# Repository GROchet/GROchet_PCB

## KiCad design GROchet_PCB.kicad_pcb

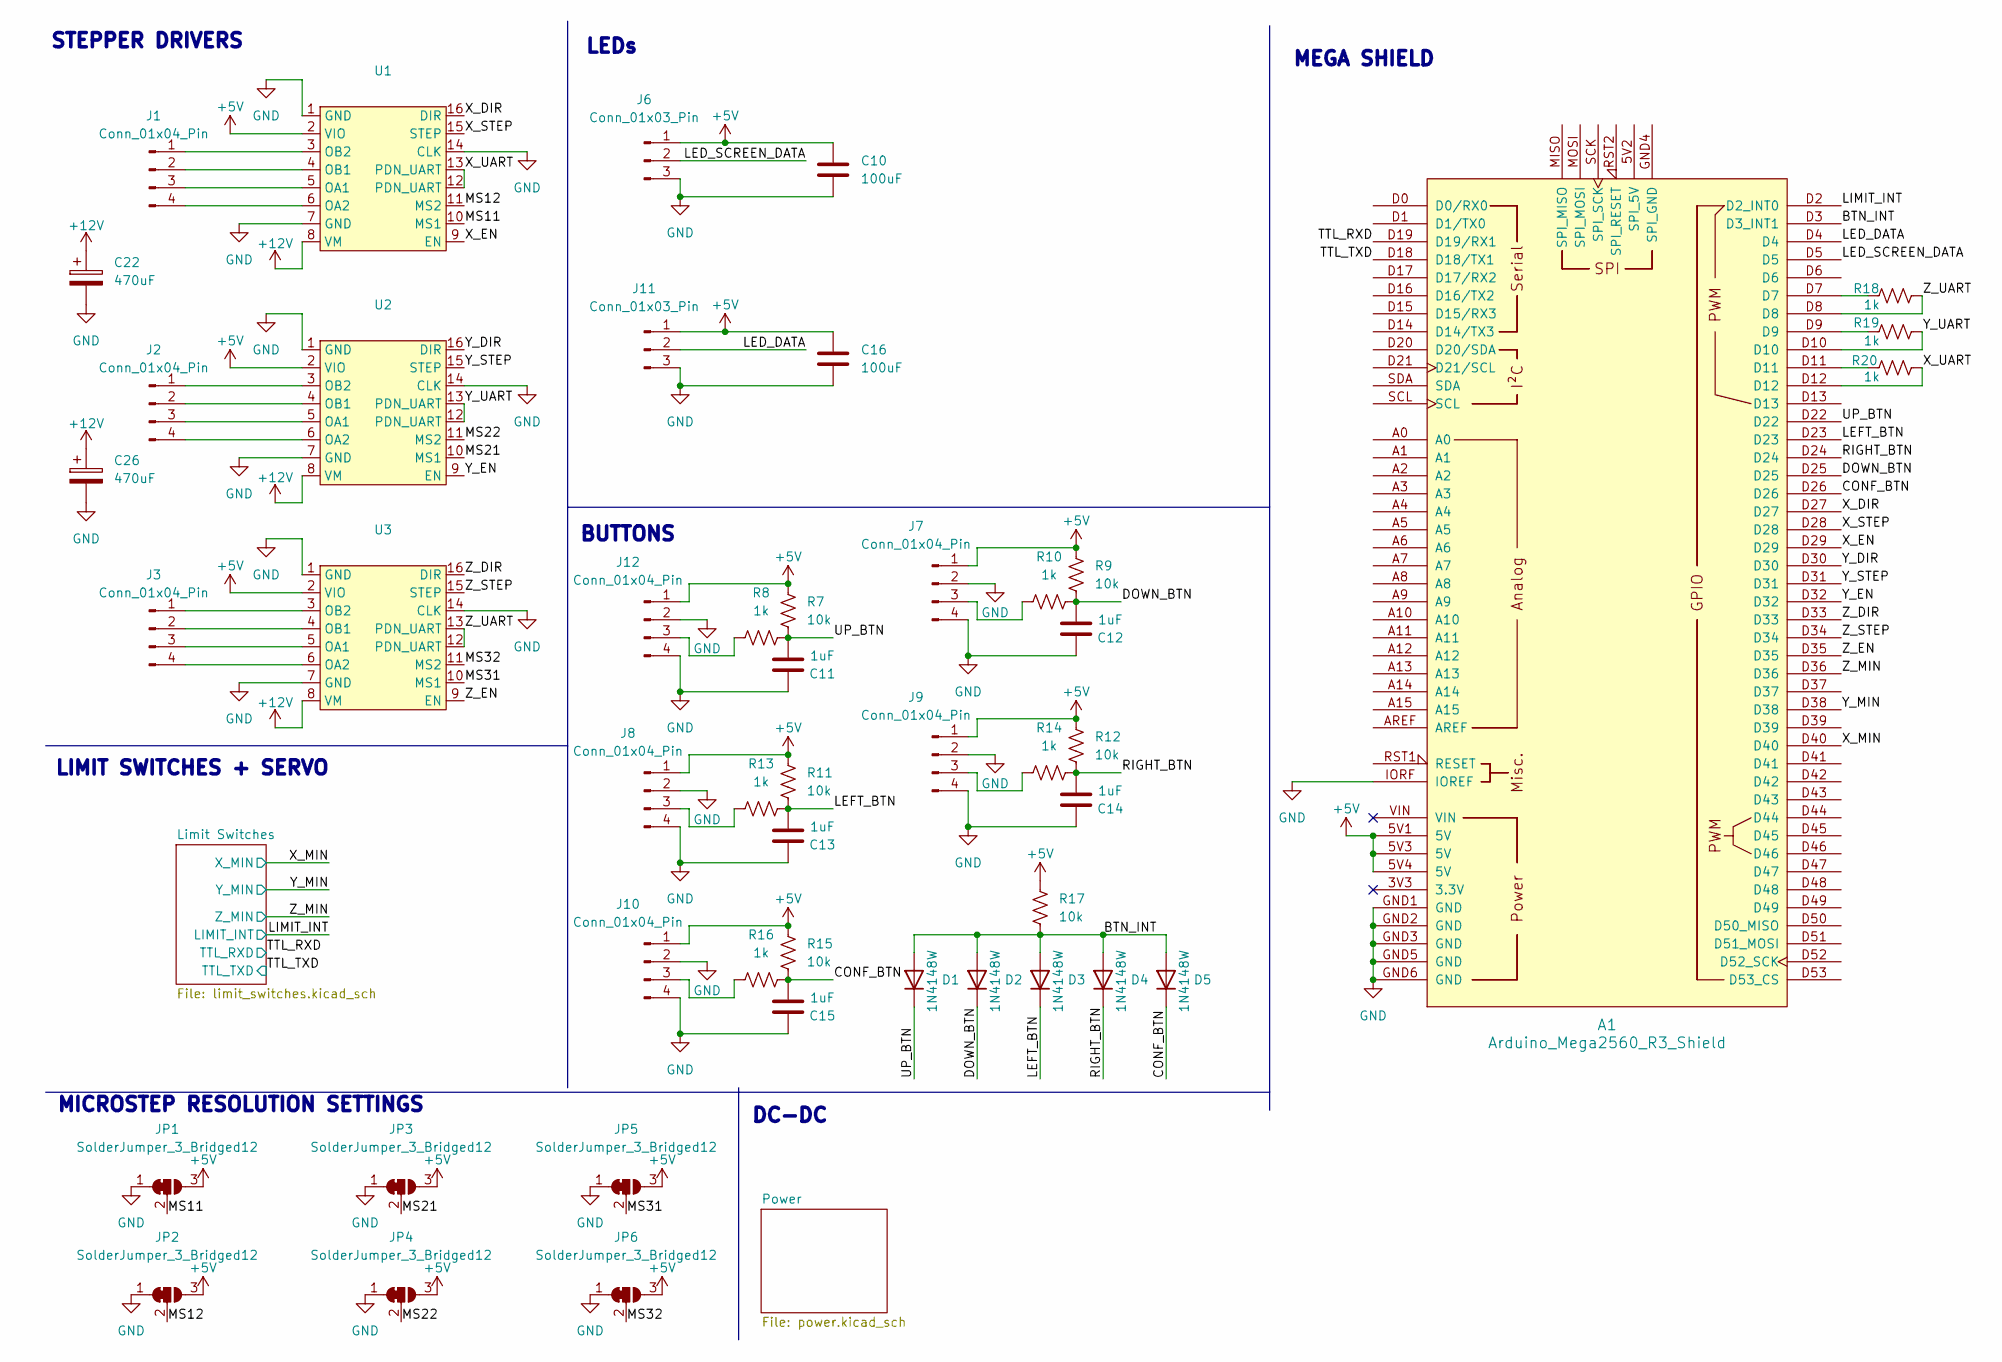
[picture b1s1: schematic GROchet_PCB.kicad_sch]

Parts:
A1: Arduino_Mega2560_R3_Shield
C10, C16: 100uF; C_1206_3216Metric; LCSC C7432784
C11, C12, C13, C14, C15: 1uF; C_0603_1608Metric_Pad1.08x0.95mm_HandSolder
C22, C26: 470uF; CP_Radial_D8.0mm_P3.50mm; LCSC C2873977
D1, D2, D3, D4, D5: 1N4148W; D_SOD-123; LCSC C83528
J1, J2, J3, J7, J8, J9, J10, J12: Conn_01x04_Pin; JST_EH_B4B-EH-A_1x04_P2.50mm_Vertical; LCSC C160258
J6, J11: Conn_01x03_Pin; JST_EH_B3B-EH-A_1x03_P2.50mm_Vertical; LCSC C144394
JP1, JP2, JP3, JP4, JP5, JP6: SolderJumper_3_Bridged12; SolderJumper-3_P1.3mm_Bridged12_RoundedPad1.0x1.5mm
R7, R9, R11, R12, R15, R17: 10k; R_0603_1608Metric_Pad0.98x0.95mm_HandSolder; LCSC C98220
R8, R10, R13, R14, R16, R18, R19, R20: 1k; R_0603_1608Metric_Pad0.98x0.95mm_HandSolder; LCSC C2907113
U1, U2, U3: TMC2208

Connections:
+5V: A1.5V1 (5V), A1.5V3 (5V), A1.5V4 (5V), C10.1, C16.1, J6.1, J7.1, J8.1, J9.1, J10.1, J11.1, J12.1, JP1.3 (B), JP2.3 (B), JP3.3 (B), JP4.3 (B), JP5.3 (B), JP6.3 (B), R7.1, R9.1, R11.1, R12.1, R15.1, R17.1, U1.2 (VIO), U2.2 (VIO), U3.2 (VIO); also elsewhere on the board
+12V: C22.1, C26.1, U1.8 (VM), U2.8 (VM), U3.8 (VM); also elsewhere on the board
/BTN_INT: A1.D3 (D3_INT1), D1.2 (A), D2.2 (A), D3.2 (A), D4.2 (A), D5.2 (A), R17.2
/CONF_BTN: A1.D26, C15.2, D5.1 (K), R15.2, R16.2
/DOWN_BTN: A1.D25, C12.2, D2.1 (K), R9.2, R10.2
/LED_DATA: A1.D4, J11.2
/LED_SCREEN_DATA: A1.D5, J6.2
/LEFT_BTN: A1.D23, C13.2, D3.1 (K), R11.2, R13.2
/LIMIT_INT: A1.D2 (D2_INT0); also elsewhere on the board
/MS11: JP1.2 (C), U1.10 (MS1)
/MS12: JP2.2 (C), U1.11 (MS2)
/MS21: JP3.2 (C), U2.10 (MS1)
/MS22: JP4.2 (C), U2.11 (MS2)
/MS31: JP5.2 (C), U3.10 (MS1)
/MS32: JP6.2 (C), U3.11 (MS2)
/RIGHT_BTN: A1.D24, C14.2, D4.1 (K), R12.2, R14.2
/TTL_RXD: A1.D19 (D19/RX1); also elsewhere on the board
/TTL_TXD: A1.D18 (D18/TX1); also elsewhere on the board
/UP_BTN: A1.D22, C11.2, D1.1 (K), R7.2, R8.2
/X_DIR: A1.D27, U1.16 (DIR)
/X_EN: A1.D29, U1.9 (EN)
/X_MIN: A1.D40; also elsewhere on the board
/X_STEP: A1.D28, U1.15 (STEP)
/X_UART: A1.D12, R20.2, U1.12 (PDN_UART), U1.13 (PDN_UART)
/Y_DIR: A1.D30, U2.16 (DIR)
/Y_EN: A1.D32, U2.9 (EN)
/Y_MIN: A1.D38; also elsewhere on the board
/Y_STEP: A1.D31, U2.15 (STEP)
/Y_UART: A1.D10, R19.2, U2.12 (PDN_UART), U2.13 (PDN_UART)
/Z_DIR: A1.D33, U3.16 (DIR)
/Z_EN: A1.D35, U3.9 (EN)
/Z_MIN: A1.D36; also elsewhere on the board
/Z_STEP: A1.D34, U3.15 (STEP)
/Z_UART: A1.D8, R18.2, U3.12 (PDN_UART), U3.13 (PDN_UART)
GND: A1.GND1 (GND), A1.GND2 (GND), A1.GND3 (GND), A1.GND5 (GND), A1.GND6 (GND), A1.IORF (IOREF), C10.2, C11.1, C12.1, C13.1, C14.1, C15.1, C16.2, C22.2, C26.2, J6.3, J7.2, J7.4, J8.2, J8.4, J9.2, J9.4, J10.2, J10.4, J11.3, J12.2, J12.4, JP1.1 (A), JP2.1 (A), JP3.1 (A), JP4.1 (A), JP5.1 (A), JP6.1 (A), U1.1 (GND), U1.7 (GND), U1.14 (CLK), U2.1 (GND), U2.7 (GND), U2.14 (CLK), U3.1 (GND), U3.7 (GND), U3.14 (CLK); also elsewhere on the board
unnamed: A1.D7, R18.1
unnamed: A1.D9, R19.1
unnamed: A1.D11, R20.1
unnamed: J1.1, U1.3 (OB2)
unnamed: J1.2, U1.4 (OB1)
unnamed: J1.3, U1.5 (OA1)
unnamed: J1.4, U1.6 (OA2)
unnamed: J2.1, U2.3 (OB2)
unnamed: J2.2, U2.4 (OB1)
unnamed: J2.3, U2.5 (OA1)
unnamed: J2.4, U2.6 (OA2)
unnamed: J3.1, U3.3 (OB2)
unnamed: J3.2, U3.4 (OB1)
unnamed: J3.3, U3.5 (OA1)
unnamed: J3.4, U3.6 (OA2)
unnamed: J7.3, R10.1
unnamed: J8.3, R13.1
unnamed: J9.3, R14.1
unnamed: J10.3, R16.1
unnamed: J12.3, R8.1

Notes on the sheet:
LEDs
BUTTONS
STEPPER DRIVERS
LIMIT SWITCHES + SERVO
MICROSTEP RESOLUTION SETTINGS
DC-DC
MEGA SHIELD

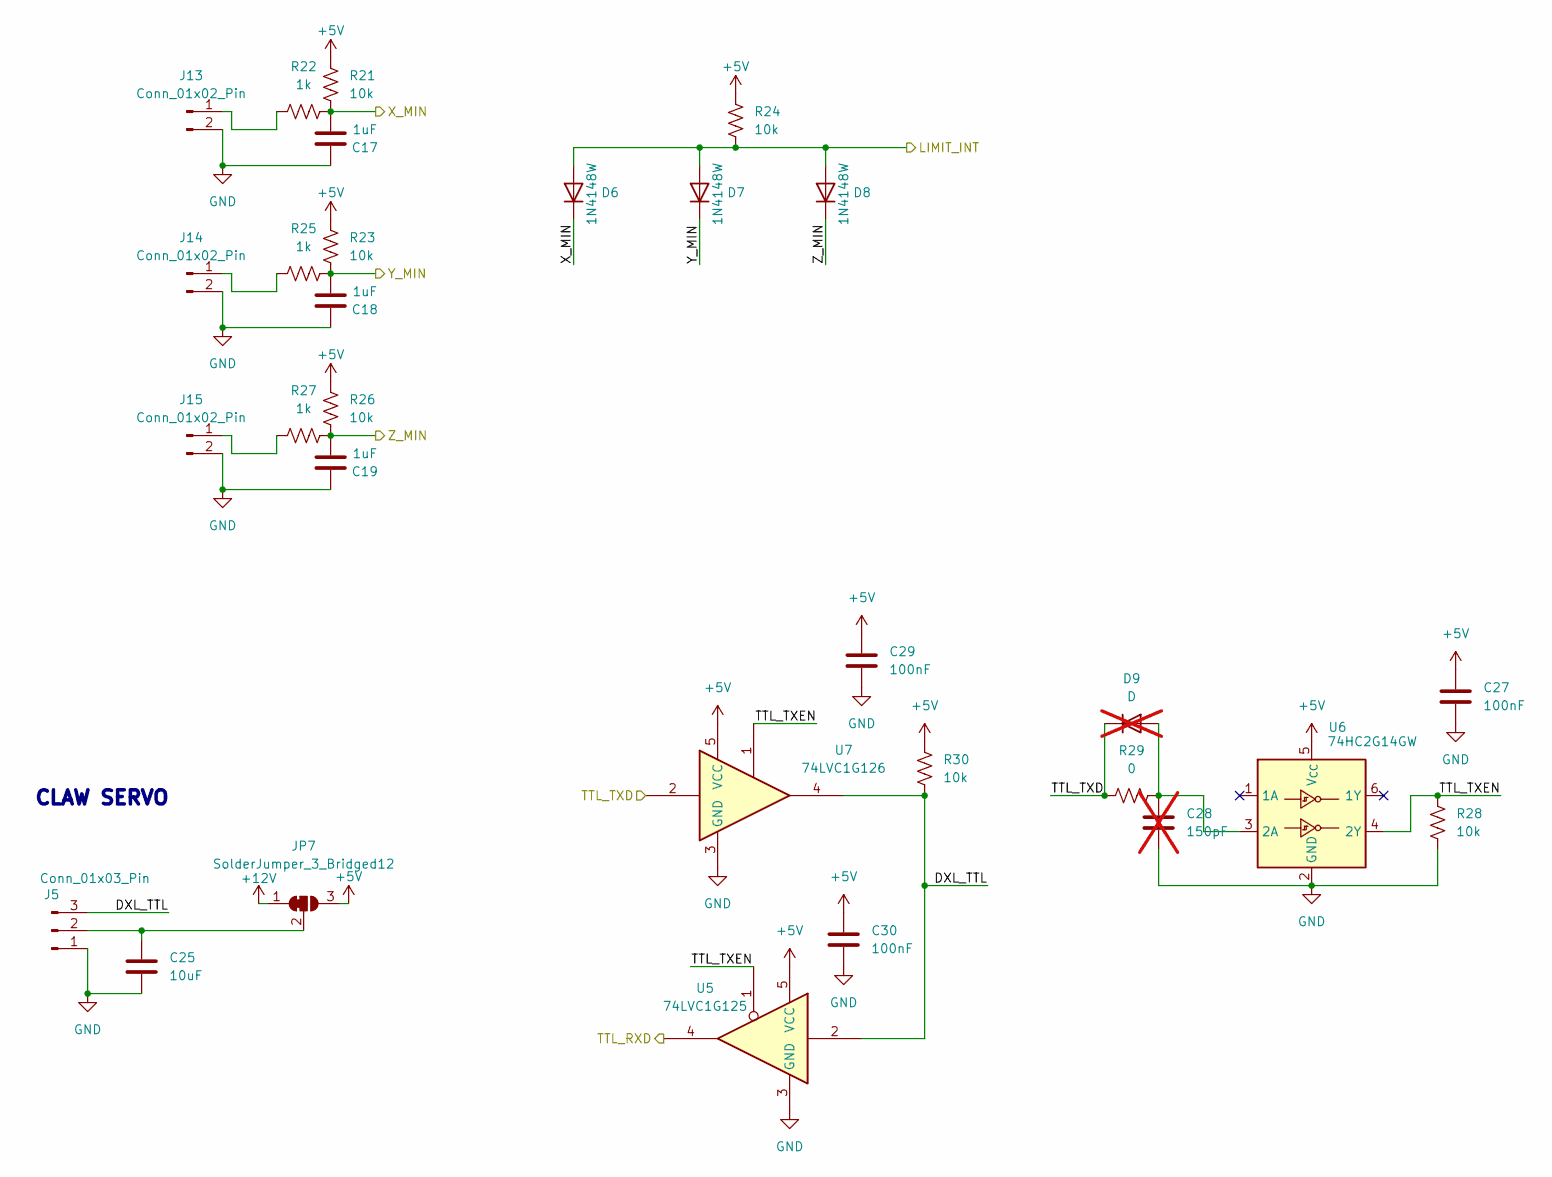
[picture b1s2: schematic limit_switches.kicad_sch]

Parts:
C17, C18, C19: 1uF; C_0603_1608Metric_Pad1.08x0.95mm_HandSolder
C25: 10uF; C_0805_2012Metric; LCSC C6119932
C27, C29, C30: 100nF; C_0603_1608Metric_Pad1.08x0.95mm_HandSolder
C28: 150pF; C_0603_1608Metric_Pad1.08x0.95mm_HandSolder; not fitted
D6, D7, D8: 1N4148W; D_SOD-123; LCSC C83528
D9: D; D_SOD-123; not fitted
J5: Conn_01x03_Pin; JST_EH_B3B-EH-A_1x03_P2.50mm_Vertical; LCSC C144394
J13, J14, J15: Conn_01x02_Pin; JST_EH_B2B-EH-A_1x02_P2.50mm_Vertical; LCSC C265281
JP7: SolderJumper_3_Bridged12; SolderJumper-3_P1.3mm_Bridged12_RoundedPad1.0x1.5mm
R21, R23, R24, R26, R28, R30: 10k; R_0603_1608Metric_Pad0.98x0.95mm_HandSolder; LCSC C98220
R22, R25, R27: 1k; R_0603_1608Metric_Pad0.98x0.95mm_HandSolder; LCSC C2907113
R29: 0; R_0603_1608Metric_Pad0.98x0.95mm_HandSolder
U5: 74LVC1G125; SOT-353_SC-70-5
U6: 74HC2G14GW; SOT-363_SC-70-6
U7: 74LVC1G126; SOT-353_SC-70-5

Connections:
+5V: C27.1, C29.1, C30.1, JP7.3 (B), R21.1, R23.1, R24.1, R26.1, R30.1, U5.5 (VCC), U6.5 (V_{CC}), U7.5 (VCC); also elsewhere on the board
+12V: JP7.1 (A); also elsewhere on the board
/LIMIT_INT: D6.2 (A), D7.2 (A), D8.2 (A), R24.2; also elsewhere on the board
/Limit Switches/DXL_TTL: J5.3, R30.2, U5.2, U7.4
/Limit Switches/TTL_TXEN: R28.1, U5.1, U6.4 (2Y), U7.1
/TTL_RXD: U5.4; also elsewhere on the board
/TTL_TXD: D9.1 (K), R29.1, U7.2; also elsewhere on the board
/X_MIN: C17.2, D6.1 (K), R21.2, R22.2; also elsewhere on the board
/Y_MIN: C18.2, D7.1 (K), R23.2, R25.2; also elsewhere on the board
/Z_MIN: C19.2, D8.1 (K), R26.2, R27.2; also elsewhere on the board
GND: C17.1, C18.1, C19.1, C25.2, C27.2, C28.2, C29.2, C30.2, J5.1, J13.2, J14.2, J15.2, R28.2, U5.3 (GND), U6.2 (GND), U7.3 (GND); also elsewhere on the board
unnamed: C28.1, D9.2 (A), R29.2, U6.3 (2A)
unnamed: C25.1, J5.2, JP7.2 (C)
unnamed: J13.1, R22.1
unnamed: J14.1, R25.1
unnamed: J15.1, R27.1

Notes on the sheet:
CLAW SERVO

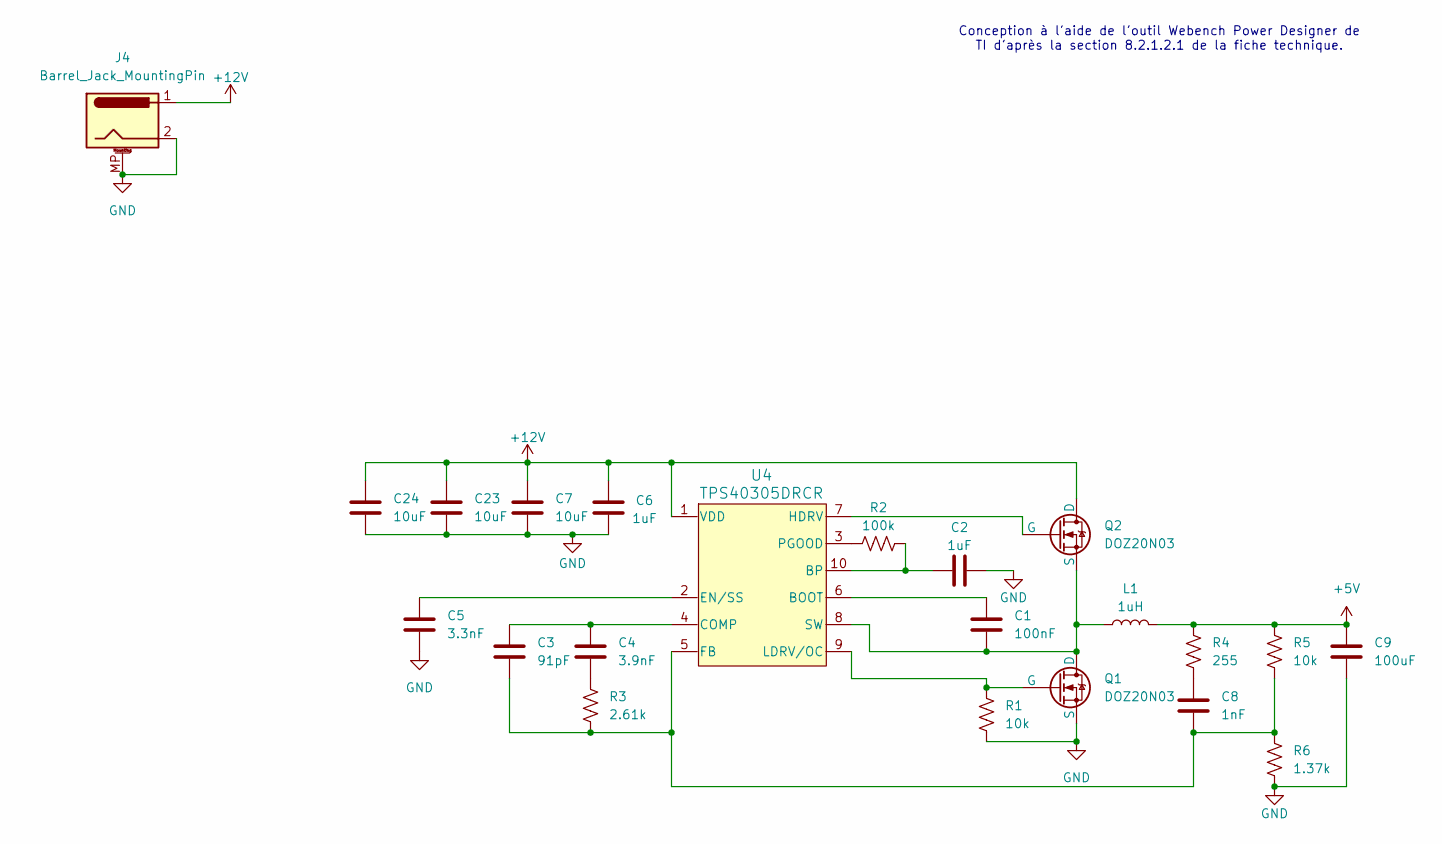
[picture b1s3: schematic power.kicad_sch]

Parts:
C1: 100nF; C_0603_1608Metric_Pad1.08x0.95mm_HandSolder
C2, C6: 1uF; C_0603_1608Metric_Pad1.08x0.95mm_HandSolder
C3: 91pF; C_0402_1005Metric_Pad0.74x0.62mm_HandSolder; LCSC C541365
C4: 3.9nF; C_0402_1005Metric_Pad0.74x0.62mm_HandSolder; LCSC C880632
C5: 3.3nF; C_0402_1005Metric_Pad0.74x0.62mm_HandSolder; LCSC C7503512
C7, C23, C24: 10uF; C_0805_2012Metric; LCSC C6119932
C8: 1nF; C_0402_1005Metric_Pad0.74x0.62mm_HandSolder; LCSC C22435950
C9: 100uF; C_1206_3216Metric; LCSC C7432784
J4: Barrel_Jack_MountingPin; BarrelJack_Wuerth_694108106102_2.5x5.5mm
L1: 1uH; L_Taiyo-Yuden_NR-60xx; LCSC C2938919
Q1, Q2: DOZ20N03; DFN-8-1EP_3x3mm_P0.5mm_EP1.7x2.4mm_ThermalVias; LCSC C41384259
R1, R5: 10k; R_0603_1608Metric_Pad0.98x0.95mm_HandSolder; LCSC C98220
R2: 100k; R_0603_1608Metric_Pad0.98x0.95mm_HandSolder; LCSC C14675
R3: 2.61k; R_0402_1005Metric_Pad0.72x0.64mm_HandSolder; LCSC C60491
R4: 255; R_0402_1005Metric_Pad0.72x0.64mm_HandSolder; LCSC C48533742
R6: 1.37k; R_0402_1005Metric_Pad0.72x0.64mm_HandSolder; LCSC C5126218
U4: TPS40305DRCR; DRC10_2P4X1P65; LCSC C140285

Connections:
+5V: C9.1, L1.2, R4.1, R5.1; also elsewhere on the board
+12V: C6.2, C7.1, C23.1, C24.1, J4.1, Q2.1 (D), U4.1 (VDD); also elsewhere on the board
GND: C2.2, C5.2, C6.1, C7.2, C9.2, C23.2, C24.2, J4.2, J4.MP (MountPin), Q1.3 (S), R1.2, R6.2; also elsewhere on the board
unnamed: C4.2, R3.1
unnamed: C8.1, R4.2
unnamed: C1.2, L1.1, Q1.1 (D), Q2.3 (S), U4.8 (SW)
unnamed: Q1.2 (G), R1.1, U4.9 (LDRV/OC)
unnamed: Q2.2 (G), U4.7 (HDRV)
unnamed: C1.1, U4.6 (BOOT)
unnamed: C2.1, R2.2, U4.10 (BP)
unnamed: C3.1, C4.1, U4.4 (COMP)
unnamed: C5.1, U4.2 (EN/SS)
unnamed: C3.2, C8.2, R3.2, R5.2, R6.1, U4.5 (FB)
unnamed: R2.1, U4.3 (PGOOD)

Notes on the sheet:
Conception à l'aide de l'outil Webench Power Designer de TI d'après la section 8.2.1.2.1 de la fiche technique.

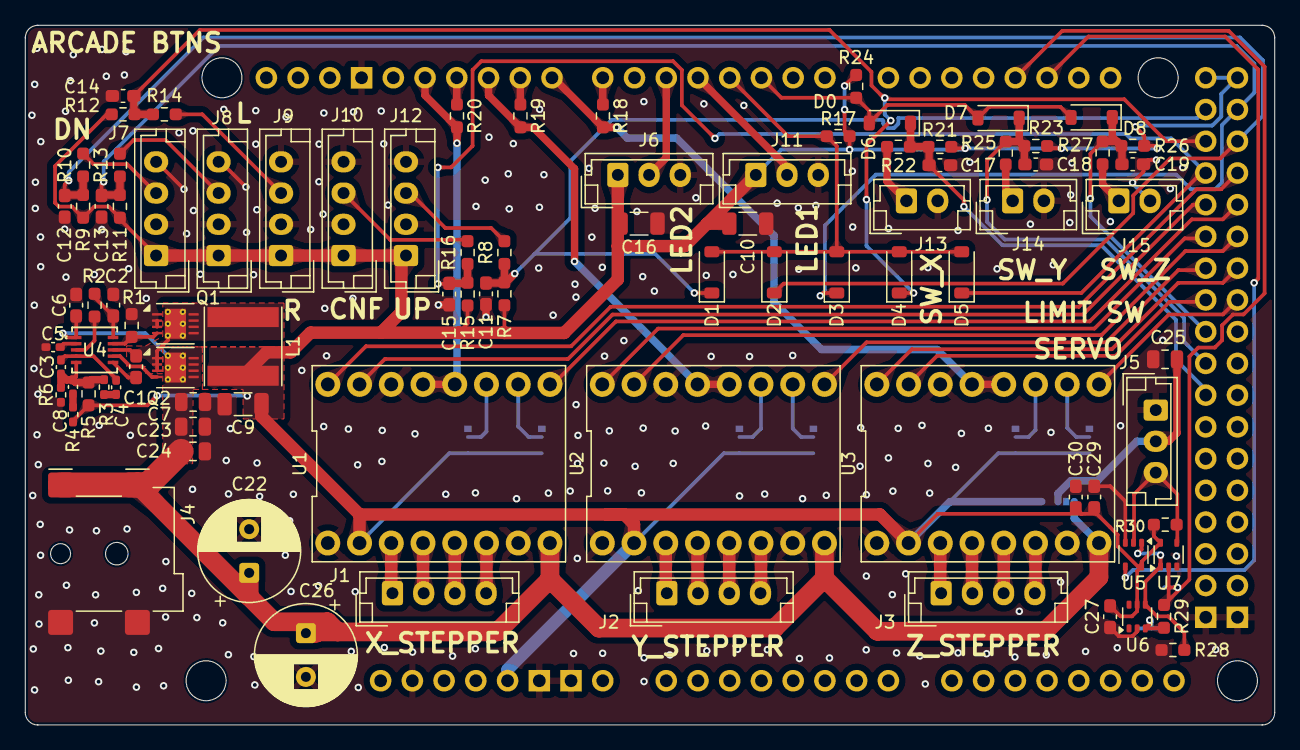
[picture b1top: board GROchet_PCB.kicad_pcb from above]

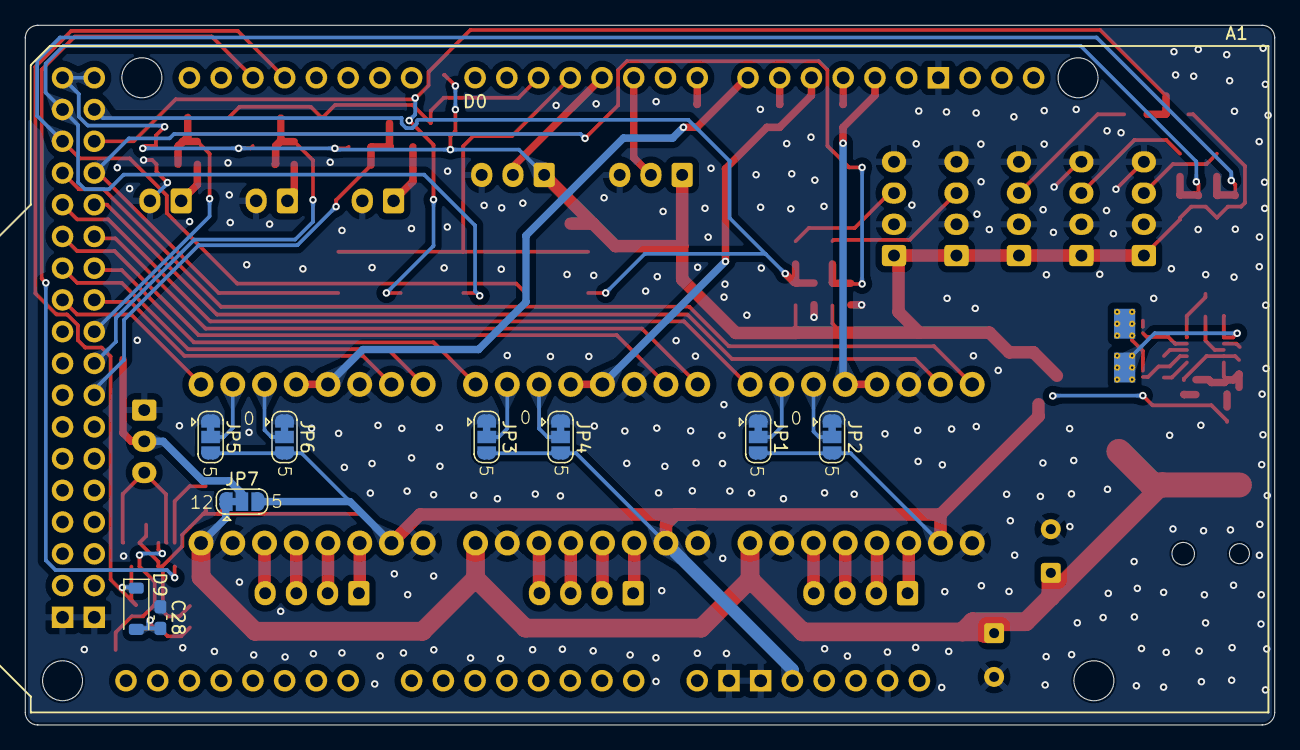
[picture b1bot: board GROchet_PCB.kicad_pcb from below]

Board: 2 copper layers, 100.0 x 56.0 mm, 100 parts (9 on the bottom side), 73 nets.

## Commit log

2026-01-23 project setup
2026-01-27 shematic design
2026-01-28 started pcb layout
2026-02-03 finished routing
2026-02-04 aaaaaaaaaaaaaaaaaa
2026-02-04 DXL Buffer circuit and new prod file
2026-02-21 Added GROchet_Bloc_Diagram.drawio
2026-02-21 Added GROchet_Bloc_Diagram.drawio.png
2026-02-21 added top view image
2026-02-21 added html bom
2026-02-24 updated schematic pdf
2026-04-15 updated bloc diagram
2026-04-15 typo correction
